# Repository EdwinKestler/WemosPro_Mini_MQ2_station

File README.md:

# WemosPro_Mini_MQ2_station
Estacion de Temperatura, Humedad y composcion de Aire por medio de sensores HTU y MQ2
## Nodo Sensorial de Temperatura, Humedad, Y compasicion del Aire. 
Este es un nodo sensorial basado en: 
* un sensor HTU21d-f ($15.51 Amazon):
[HTU Amazon](https://www.amazon.com/Adafruit-HTU21D-F-Temperature-Humidity-Breakout/dp/B00OKJFLWO/ref=sr_1_2?ie=UTF8&qid=1533595116&sr=8-2&keywords=HTU21d-f+sensor%2B&dpID=61SQP6J6LzL&preST=_SX300_QL70_&dpSrc=srch)
* un sensor de humo MQ2 ($6.99 amazon):
[MQ2 Amazon](https://www.amazon.com/SUKRAGRAHA-Detector-Module-Arduino-Genuino/dp/B01F2X3VY6/ref=sr_1_3?s=electronics&rps=1&ie=UTF8&qid=1533595239&sr=1-3&keywords=mq2+gas+sensor&refinements=p_85%3A2470955011)
* un modulo ESP866 (WEMOSD1 MINI pro, $9.99 Amazon):
[WEMOS Amazon](https://www.amazon.com/Aideepen-WEMOS-Mini-Pro-Connector/dp/B07333L9VR/ref=sr_1_3?s=electronics&ie=UTF8&qid=1533595295&sr=1-3&keywords=wemos+d1+mini+pro)
* un modulo de manejo de energia y carga solar (Li-po Rider v1.1 seeedstudio, $15.01 Amazon)
[Harvesting Amazon](https://www.amazon.com/Aideepen-WEMOS-Mini-Pro-Connector/dp/B07333L9VR/ref=sr_1_3?s=electronics&ie=UTF8&qid=1533595295&sr=1-3&keywords=wemos+d1+mini+pro)
* un Panel Solar de 5V 500mA 2.5W ($15.99 Amazon)
[Panel Amazon](https://www.amazon.com/ALLPOWERS-Battery-Charger-Encapsulated-130x150mm/dp/B074TYH68Z/ref=sr_1_3?ie=UTF8&qid=1533595591&sr=8-3&keywords=solar+panel+5W+5V)
* una Bateria Lipo de 3,000 mah 3.7V ($11.49 Amazon)
[Batteria Amazon](https://www.amazon.com/YDL-3000mAh-battery-Rechargeable-Connector/dp/B07BTV1SCB/ref=sr_1_14_a_it?ie=UTF8&qid=1533595692&sr=8-14&keywords=3000+mah+lipo)
* una caja plastica IP55 para exteriores ($7.5 Amazon)
[Caja Exteriores Amazon](https://www.amazon.com/LeMotech-Dustproof-Waterproof-Electrical-85mmx85mmx50mm/dp/B075X14RVH/ref=sr_1_1?ie=UTF8&qid=1533595799&sr=8-1&keywords=ip55+plastic+outdoor&dpID=31Wrm5nBbmL&preST=_SY300_QL70_&dpSrc=srch)
* Ultracapacitores 2.8 15F Vishay y diodo (x3 $5.82 Mouser):
[Solar Harvesting](https://www.mouser.com/ProductDetail/Vishay-BC-Components/MAL219691252E3?qs=sGAEpiMZZMsCu9HefNWqpofZ%252b8Ak8%2fFpWUg8YRD9hhHpGlA0UuQd1w%3d%3d)
* Alambre de amarre y otros compenetes discretos ($5 varios locales)
* una caja plastica tensparente pequeña (set de 100 piezas $14.99 amazon).
[cajas para Oled y sensor HTU](https://www.amazon.com/Plastic-Empty-Watercolour-100Pcs-Transparent/dp/B07CF7PQFQ/ref=sr_1_32?ie=UTF8&qid=1533596358&sr=8-32&keywords=outdoor+transparent+plastic+box+small)

# Total costo:  $119.93

### esquematicos
* EagleCad 9.1.2:
    * Schematic:
    
    * Board:
    
* link para pedido en OSHPARK:
[OSHPARK](https://oshpark.com/shared_projects/FCERSQkG)
* Imagenes de Board:
    * Top:
    
    * Botom:
    
### Fotografias

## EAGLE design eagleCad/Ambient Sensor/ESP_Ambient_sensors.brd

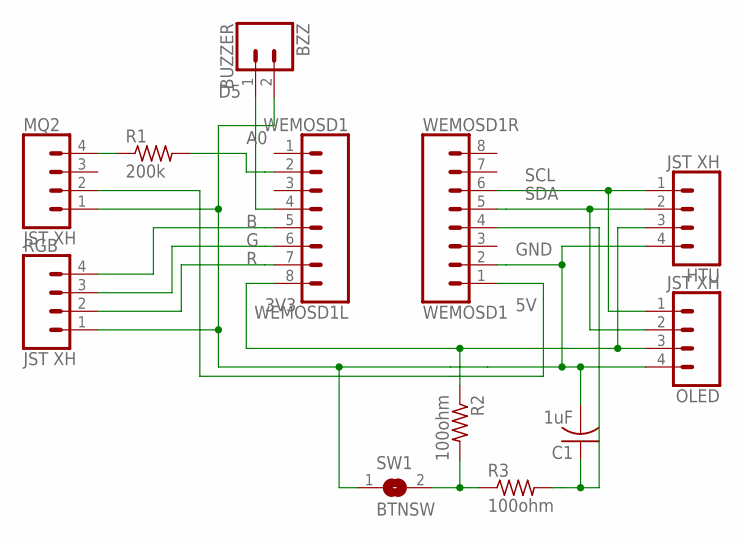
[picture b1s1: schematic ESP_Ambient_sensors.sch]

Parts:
BZZ: BUZZER; 1X02
C1: 1uF; C0805
HTU: JST XH; 1X04
MQ2: JST XH; 1X04
OLED: JST XH; 1X04
R1: 200k; R0805
R2, R3: 100ohm; R0805
RGB: JST XH; 1X04
SW1: BTNSW; SJW
WEMOSD1L, WEMOSD1R: WEMOSD1; 1X08

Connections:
3V3: HTU.3, OLED.3, R2.1, WEMOSD1L.8
5V: MQ2.2, WEMOSD1R.1
A0: R1.2, WEMOSD1L.2
B: RGB.4, WEMOSD1L.5
D5: BZZ.1, WEMOSD1L.4
G: RGB.3, WEMOSD1L.6
GND: BZZ.2, C1.2, HTU.4, MQ2.1, OLED.4, RGB.1, SW1.1, WEMOSD1R.2
unnamed: R2.2, R3.1, SW1.2
unnamed: C1.1, R3.2, WEMOSD1R.4
unnamed: MQ2.4, R1.1
R: RGB.2, WEMOSD1L.7
SCL: HTU.1, OLED.1, WEMOSD1R.6
SDA: HTU.2, OLED.2, WEMOSD1R.5

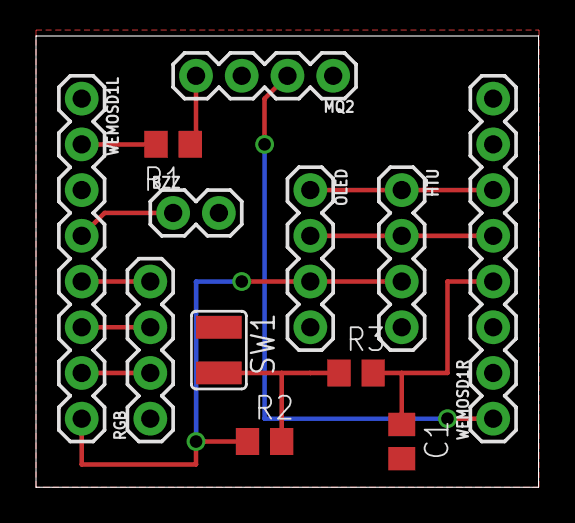
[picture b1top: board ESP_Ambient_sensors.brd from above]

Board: 2 copper layers, 27.9 x 25.1 mm, 12 parts (0 on the bottom side), 13 nets.

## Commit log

2018-08-03 intial commit
2018-08-03 First Compile
2018-08-03 spaces
2018-08-03 port monitor
2018-08-03 changed baudrate
2018-08-03 changed to case states temperture and humidity
2018-08-06 updated reasme in github
2018-08-06 editado el Readme
2018-08-06 Archivo readme creado
    creado archivo
2018-08-06 documentacion
2018-08-06 added images
    se subieron las fotos
2018-08-06 se adicionaron imagenes
2018-08-06 se corrigio el markdown
2018-08-06 Cambios de documnentacion
2018-08-06 Actualizacion de Costo
2018-08-06 cambio uno
2018-08-06 licencense opensource hardware
2018-08-06 Licence MIT
2018-08-06 licencia

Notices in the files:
parts and their libraries:
SparkFun-Connectors: Licensing: Creative Commons ShareAlike 4.0 International - https://creativecommons.org/licenses/by-sa/4.0
